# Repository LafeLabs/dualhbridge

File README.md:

# dualhbridge
Dual H bridge board files of all kinds

Most recent version is v4

Boards are available from pcbway

all designs are public domain with no restrictions whatsoever.

| part description | part number | link|
|------------------|-------------|-----|
|                  |             |     |

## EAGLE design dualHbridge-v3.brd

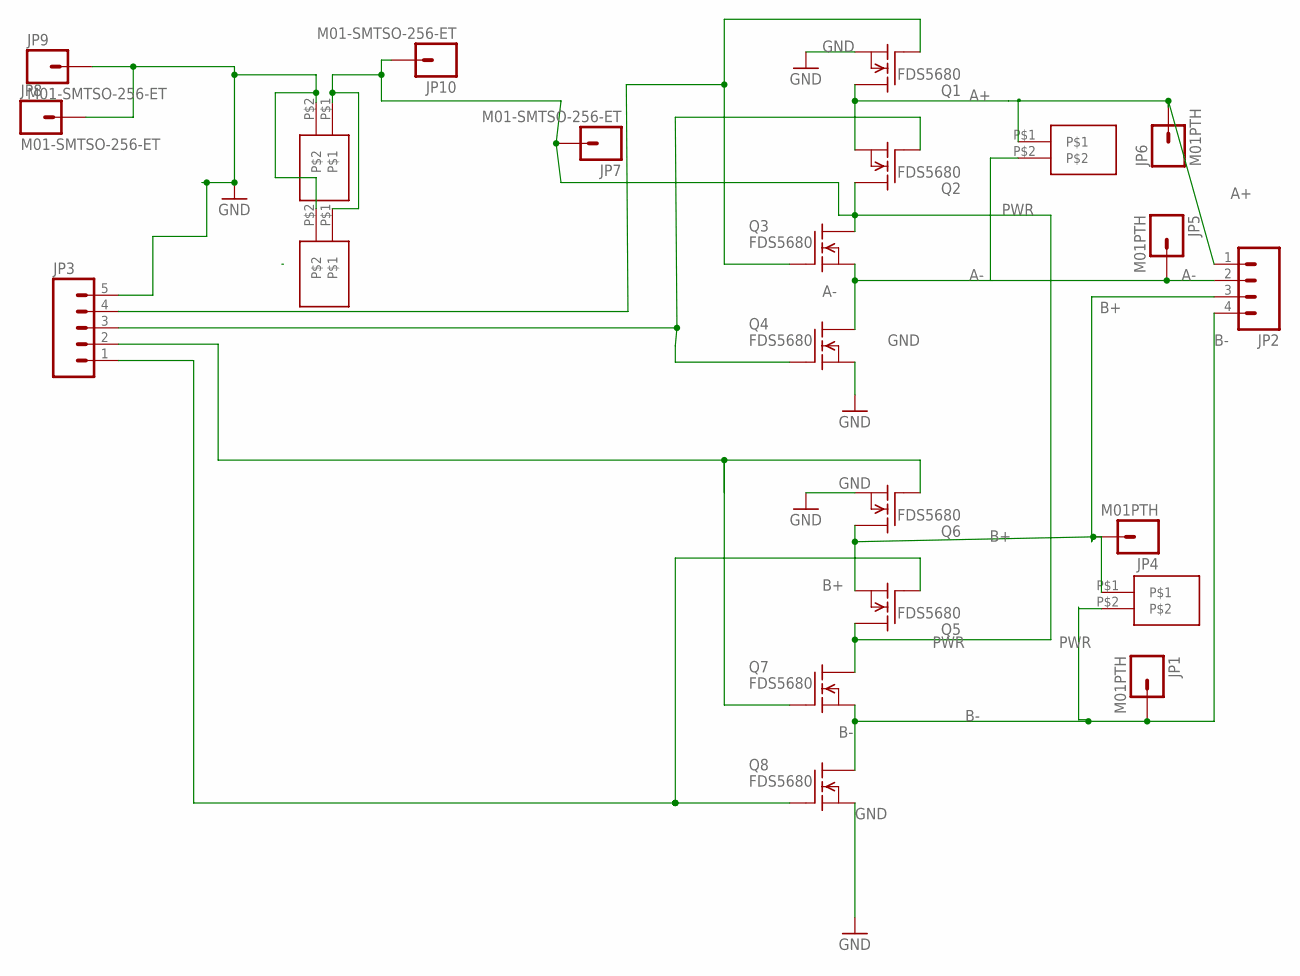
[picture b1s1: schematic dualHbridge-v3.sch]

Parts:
JP1, JP4, JP5, JP6: M01PTH; 1X01
JP2: M04LONGPADS; 1X04_LONGPADS
JP3: M05PTH; 1X05
JP7, JP8, JP9, JP10: M01-SMTSO-256-ET; SMTSO-256-ET
Q1, Q2, Q3, Q4, Q5, Q6, Q7, Q8: FDS5680; SO-8
U$1, U$2, U$3, U$4: SPRING-TERMINAL

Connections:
A+: JP2.1, JP6.1, Q1.5 (D), Q1.6 (D), Q1.7 (D), Q1.8 (D), Q2.1 (S), Q2.2 (S), Q2.3 (S), U$1.P$1
A-: JP2.2, JP5.1, Q3.1 (S), Q3.2 (S), Q3.3 (S), Q4.5 (D), Q4.6 (D), Q4.7 (D), Q4.8 (D), U$1.P$2
B+: JP2.3, JP4.1, Q5.1 (S), Q5.2 (S), Q5.3 (S), Q6.5 (D), Q6.6 (D), Q6.7 (D), Q6.8 (D), U$3.P$1
B-: JP1.1, JP2.4, Q7.1 (S), Q7.2 (S), Q7.3 (S), Q8.5 (D), Q8.6 (D), Q8.7 (D), Q8.8 (D), U$3.P$2
GND: JP3.5, JP8.P$1, JP9.P$1, Q1.1 (S), Q1.2 (S), Q1.3 (S), Q4.1 (S), Q4.2 (S), Q4.3 (S), Q6.1 (S), Q6.2 (S), Q6.3 (S), Q8.1 (S), Q8.2 (S), Q8.3 (S), U$2.P$2, U$4.P$2
unnamed: JP3.3, Q2.4 (G), Q4.4 (G)
unnamed: JP3.4, Q1.4 (G), Q3.4 (G)
unnamed: JP3.2, Q6.4 (G), Q7.4 (G)
unnamed: JP3.1, Q5.4 (G), Q8.4 (G)
PWR: JP7.P$1, JP10.P$1, Q2.5 (D), Q2.6 (D), Q2.7 (D), Q2.8 (D), Q3.5 (D), Q3.6 (D), Q3.7 (D), Q3.8 (D), Q5.5 (D), Q5.6 (D), Q5.7 (D), Q5.8 (D), Q7.5 (D), Q7.6 (D), Q7.7 (D), Q7.8 (D), U$2.P$1, U$4.P$1

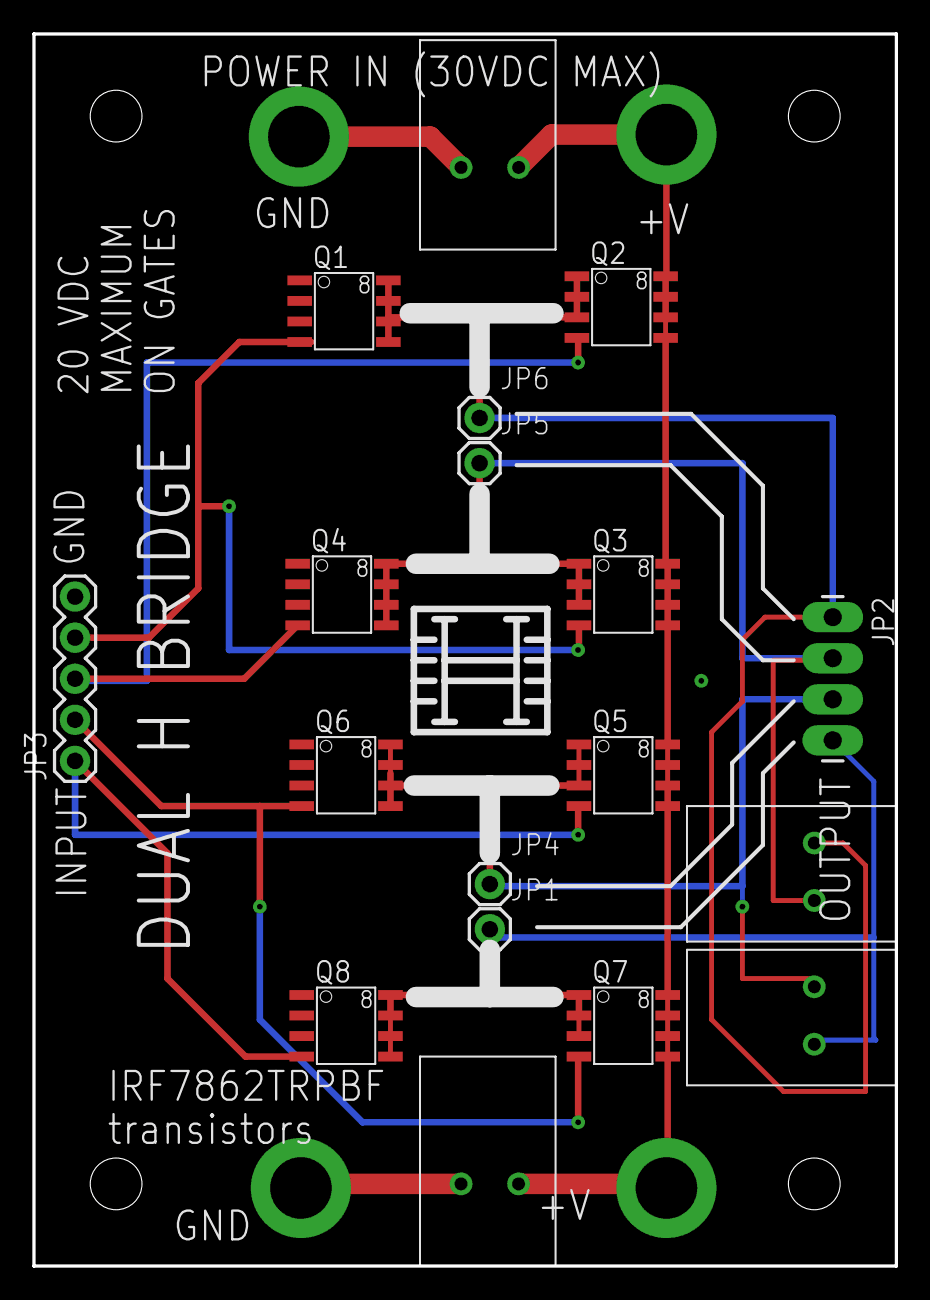
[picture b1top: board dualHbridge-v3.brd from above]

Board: 2 copper layers, 53.3 x 76.2 mm, 22 parts (0 on the bottom side), 10 nets.

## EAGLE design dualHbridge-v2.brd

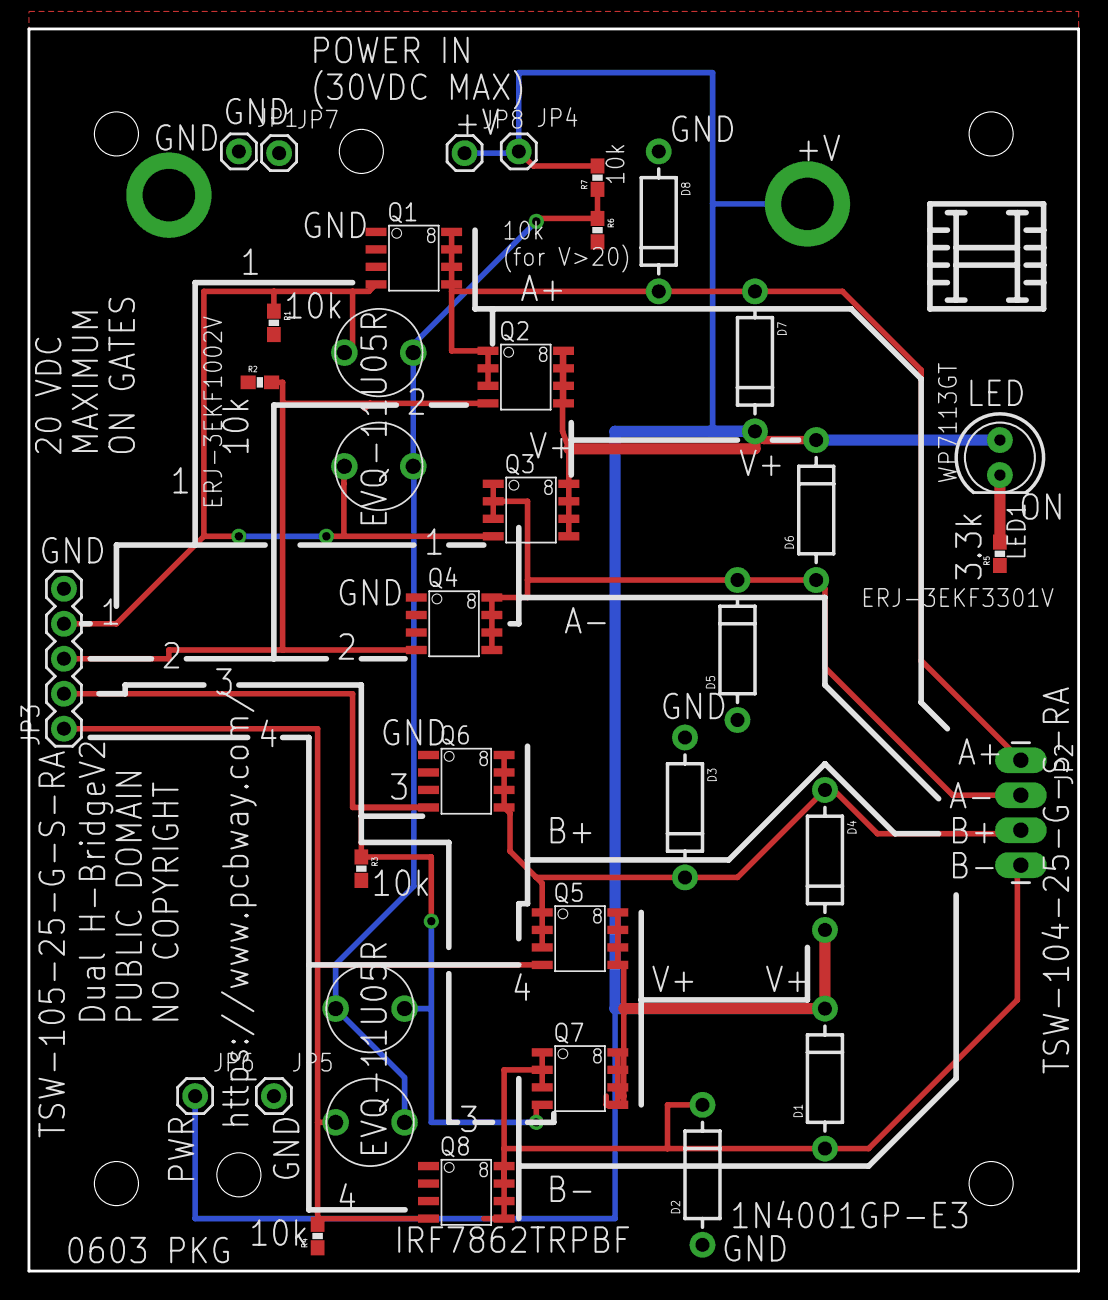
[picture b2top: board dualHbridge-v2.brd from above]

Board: 2 copper layers, 76.2 x 90.2 mm, 38 parts (0 on the bottom side), 12 nets.

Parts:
D1, D2, D3, D4, D5, D6, D7, D8: DIODE-1N4001-KIT
JP1, JP4, JP5, JP6, JP7, JP8: M01PTH; 1X01
JP2: 1X04_LONGPADS
JP3: 1X05
JP9, JP10: M01-SMTSO-256-ET; SMTSO-256-ET
LED1: LED5MM
Q1, Q2, Q3, Q4, Q5, Q6, Q7, Q8: FDS5680; SO-8
R1, R2, R3, R4, R6, R7: 10k; 0603-RES
R5: 3.3k; 0603-RES
U$1, U$2, U$3, U$4: BUTTON

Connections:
12V: D1.C, D4.C, D6.C, D7.C, JP4.1, JP6.1, JP8.1, JP10.P$1, LED1.A, Q2.5, Q2.6, Q2.7, Q2.8, Q3.5, Q3.6, Q3.7, Q3.8, Q5.5, Q5.6, Q5.7, Q5.8, Q7.5, Q7.6, Q7.7, Q7.8, R7.2
A+: D7.A, D8.C, JP2.1, Q1.5, Q1.6, Q1.7, Q1.8, Q2.1, Q2.2, Q2.3
A-: D5.C, D6.A, JP2.2, Q3.1, Q3.2, Q3.3, Q4.5, Q4.6, Q4.7, Q4.8
B+: D3.C, D4.A, JP2.3, Q5.1, Q5.2, Q5.3, Q6.5, Q6.6, Q6.7, Q6.8
B-: D1.A, D2.C, JP2.4, Q7.1, Q7.2, Q7.3, Q8.5, Q8.6, Q8.7, Q8.8
GND: D2.A, D3.A, D5.A, D8.A, JP1.1, JP3.5, JP5.1, JP7.1, JP9.P$1, Q1.1, Q1.2, Q1.3, Q4.1, Q4.2, Q4.3, Q6.1, Q6.2, Q6.3, Q8.1, Q8.2, Q8.3, R1.2, R2.1, R3.2, R4.1, R5.1, R6.2
unnamed: LED1.K, R5.2
unnamed: JP3.4, Q1.4, Q3.4, R1.1, U$3.P$1, U$4.P$1
unnamed: JP3.3, Q2.4, Q4.4, R2.2
unnamed: R6.1, R7.1, U$1.P$2, U$2.P$2, U$3.P$2, U$4.P$2
unnamed: JP3.2, Q6.4, Q7.4, R3.1, U$2.P$1
unnamed: JP3.1, Q5.4, Q8.4, R4.2, U$1.P$1

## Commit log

2019-01-24 put the files in the repo
2019-01-25 boms added, including new one for v4
2019-01-25 attempting table usage in markdown with great skepticism
2019-01-25 random updates
2019-01-25 bom updates

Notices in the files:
parts and their libraries:
SparkFun-Connectors: Licensing: Creative Commons ShareAlike 4.0 International - https://creativecommons.org/licenses/by-sa/4.0
